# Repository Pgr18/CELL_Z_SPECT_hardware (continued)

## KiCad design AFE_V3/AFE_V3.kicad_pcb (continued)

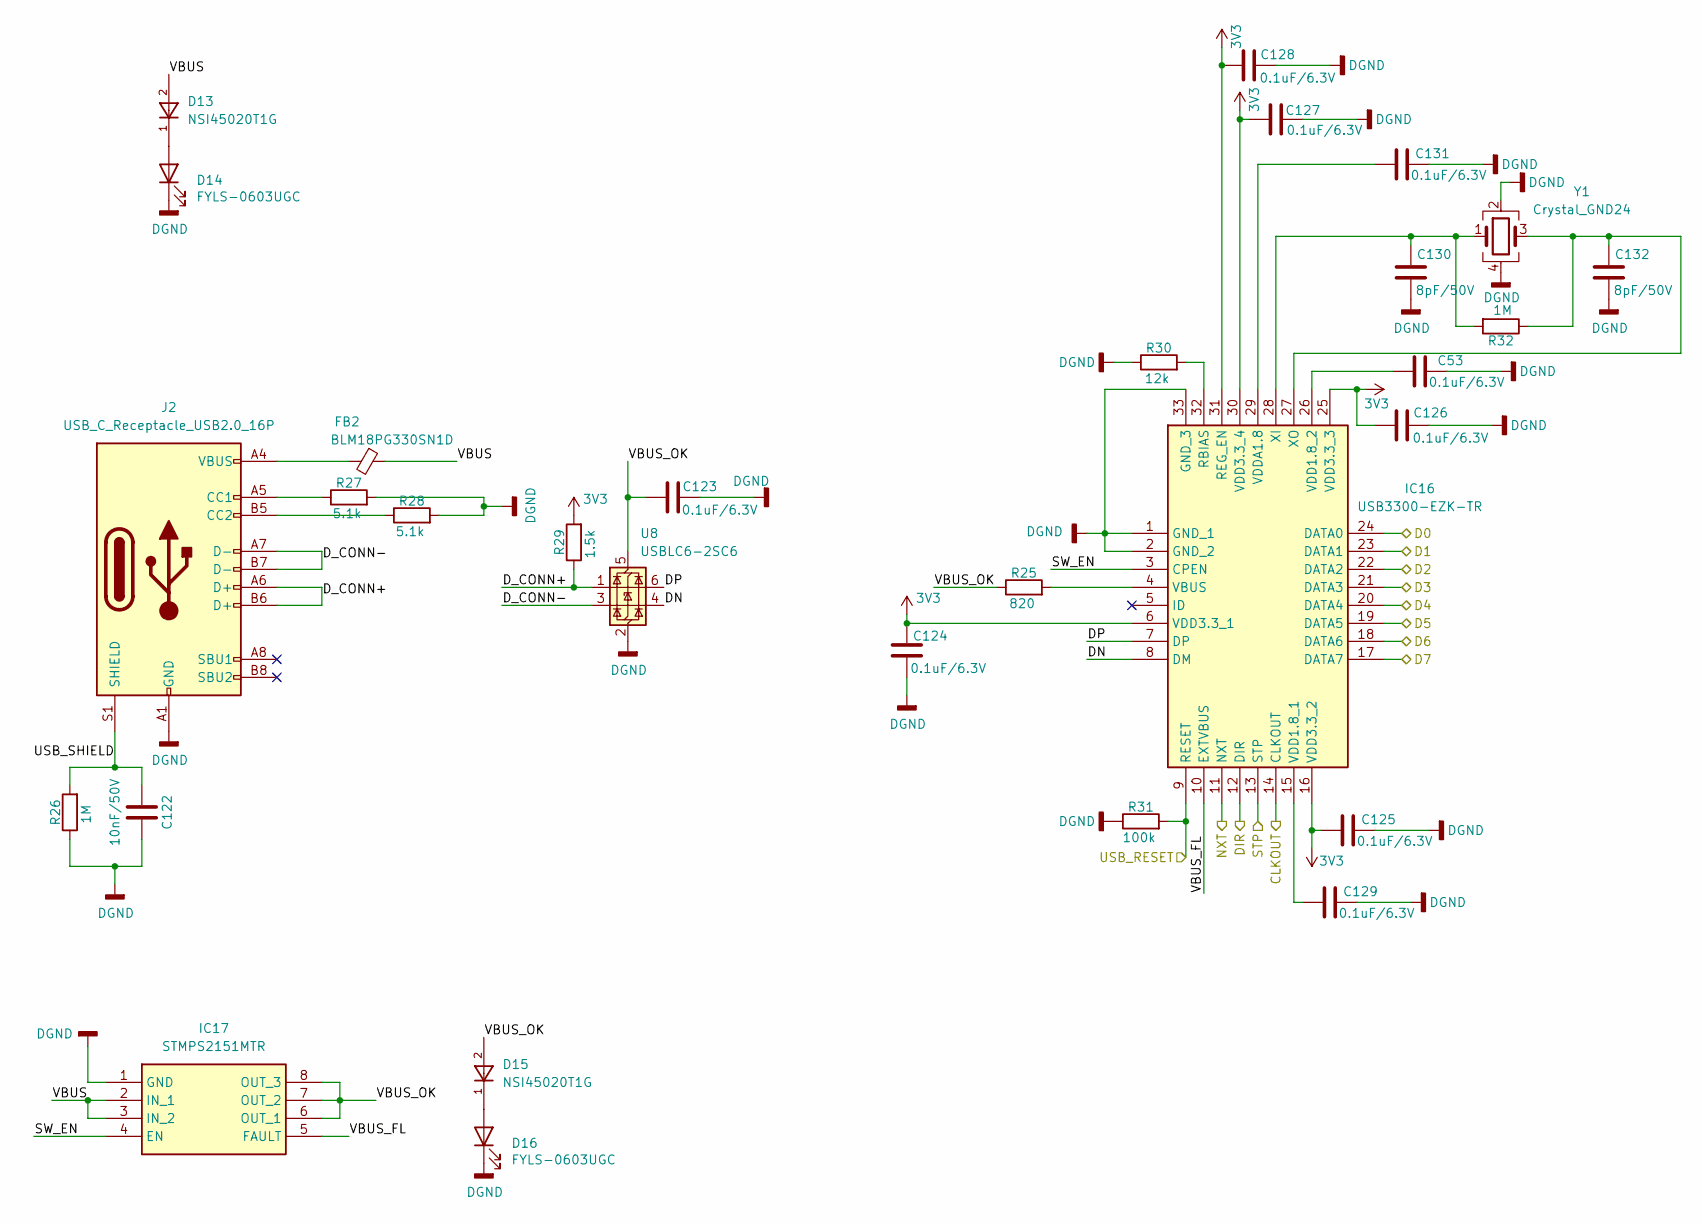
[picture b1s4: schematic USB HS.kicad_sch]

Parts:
C53, C123, C124, C125, C126, C127, C128, C129, C131: 0.1uF/6.3V; C_0603_1608Metric_Pad1.08x0.95mm_HandSolder
C122: 10nF/50V; C_0603_1608Metric_Pad1.08x0.95mm_HandSolder
C130, C132: 8pF/50V; C_0402_1005Metric_Pad0.74x0.62mm_HandSolder
D13, D15: NSI45020T1G; SOD3716X135N; PARTREV 6
D14, D16: FYLS-0603UGC; LED_0603_1608Metric_Pad1.05x0.95mm_HandSolder
FB2: BLM18PG330SN1D; L_0603_1608Metric_Pad1.05x0.95mm_HandSolder
IC16: USB3300-EZK-TR; QFN50P500X500X100-33N-D; Manufacturer_Part_Number USB3300-EZK-TR
IC17: STMPS2151MTR; SOIC127P600X175-8N; Manufacturer_Part_Number STMPS2151MTR; Mouser Part Number 511-STMPS2151MTR
J2: USB_C_Receptacle_USB2.0_16P; USB_C_Receptacle_GCT_USB4110
R25: 820; R_0805_2012Metric_Pad1.20x1.40mm_HandSolder
R26, R32: 1M; R_0805_2012Metric_Pad1.20x1.40mm_HandSolder
R27, R28: 5.1k; R_0603_1608Metric_Pad0.98x0.95mm_HandSolder
R29: 1.5k; R_0603_1608Metric_Pad0.98x0.95mm_HandSolder
R30: 12k; R_0805_2012Metric_Pad1.20x1.40mm_HandSolder
R31: 100k; R_0603_1608Metric
U8: USBLC6-2SC6; SOT-23-6
Y1: Crystal_GND24; Crystal_SMD_SeikoEpson_FA238-4Pin_3.2x2.5mm

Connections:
3V3: C124.1, C125.1, C126.1, C127.1, C128.1, IC16.6 (VDD3.3_1), IC16.16 (VDD3.3_2), IC16.25 (VDD3.3_3), IC16.30 (VDD3.3_4), IC16.31 (REG_EN), R29.2; also elsewhere on the board
/ULPI_CK: IC16.14 (CLKOUT); also elsewhere on the board
/ULPI_D0: IC16.24 (DATA0); also elsewhere on the board
/ULPI_D1: IC16.23 (DATA1); also elsewhere on the board
/ULPI_D2: IC16.22 (DATA2); also elsewhere on the board
/ULPI_D3: IC16.21 (DATA3); also elsewhere on the board
/ULPI_D4: IC16.20 (DATA4); also elsewhere on the board
/ULPI_D5: IC16.19 (DATA5); also elsewhere on the board
/ULPI_D6: IC16.18 (DATA6); also elsewhere on the board
/ULPI_D7: IC16.17 (DATA7); also elsewhere on the board
/ULPI_DIR: IC16.12 (DIR); also elsewhere on the board
/ULPI_NXT: IC16.11 (NXT); also elsewhere on the board
/ULPI_STP: IC16.13 (STP); also elsewhere on the board
/USB HS/DN: IC16.8 (DM), U8.4 (I/O2)
/USB HS/DP: IC16.7 (DP), U8.6 (I/O1)
/USB HS/D_CONN+: J2.A6 (D+), J2.B6 (D+), R29.1, U8.1 (I/O1)
/USB HS/D_CONN-: J2.A7 (D-), J2.B7 (D-), U8.3 (I/O2)
/USB HS/SW_EN: IC16.3 (CPEN), IC17.4 (EN)
/USB HS/USB_SHIELD: C122.1, J2.S1 (SHIELD), R26.2
/USB HS/VBUS: D13.2, FB2.1, IC17.2 (IN_1), IC17.3 (IN_2)
/USB HS/VBUS_FL: IC16.10 (EXTVBUS), IC17.5 (FAULT)
/USB HS/VBUS_OK: C123.2, D15.2, IC17.6 (OUT_1), IC17.7 (OUT_2), IC17.8 (OUT_3), R25.1, U8.5 (VBUS)
/USB_RESET: IC16.9 (RESET), R31.2; also elsewhere on the board
DGND: C53.2, C122.2, C123.1, C124.2, C125.2, C126.2, C127.2, C128.2, C129.2, C130.1, C131.2, C132.1, D14.1 (K), D16.1 (K), IC16.1 (GND_1), IC16.2 (GND_2), IC16.33 (GND_3), IC17.1 (GND), J2.A1 (GND), J2.A12 (GND), J2.B1 (GND), J2.B12 (GND), R26.1, R27.2, R28.2, R30.1, R31.1, U8.2 (GND), Y1.2, Y1.4; also elsewhere on the board
unnamed: D13.1, D14.2 (A)
unnamed: D15.1, D16.2 (A)
unnamed: FB2.2, J2.A4 (VBUS), J2.A9 (VBUS), J2.B4 (VBUS), J2.B9 (VBUS)
unnamed: IC16.32 (RBIAS), R30.2
unnamed: IC16.4 (VBUS), R25.2
unnamed: C129.1, IC16.15 (VDD1.8_1)
unnamed: C53.1, IC16.26 (VDD1.8_2)
unnamed: C131.1, IC16.29 (VDDA1.8)
unnamed: C130.2, IC16.28 (XI), R32.2, Y1.1
unnamed: C132.2, IC16.27 (XO), R32.1, Y1.3
unnamed: J2.A5 (CC1), R27.1
unnamed: J2.B5 (CC2), R28.1

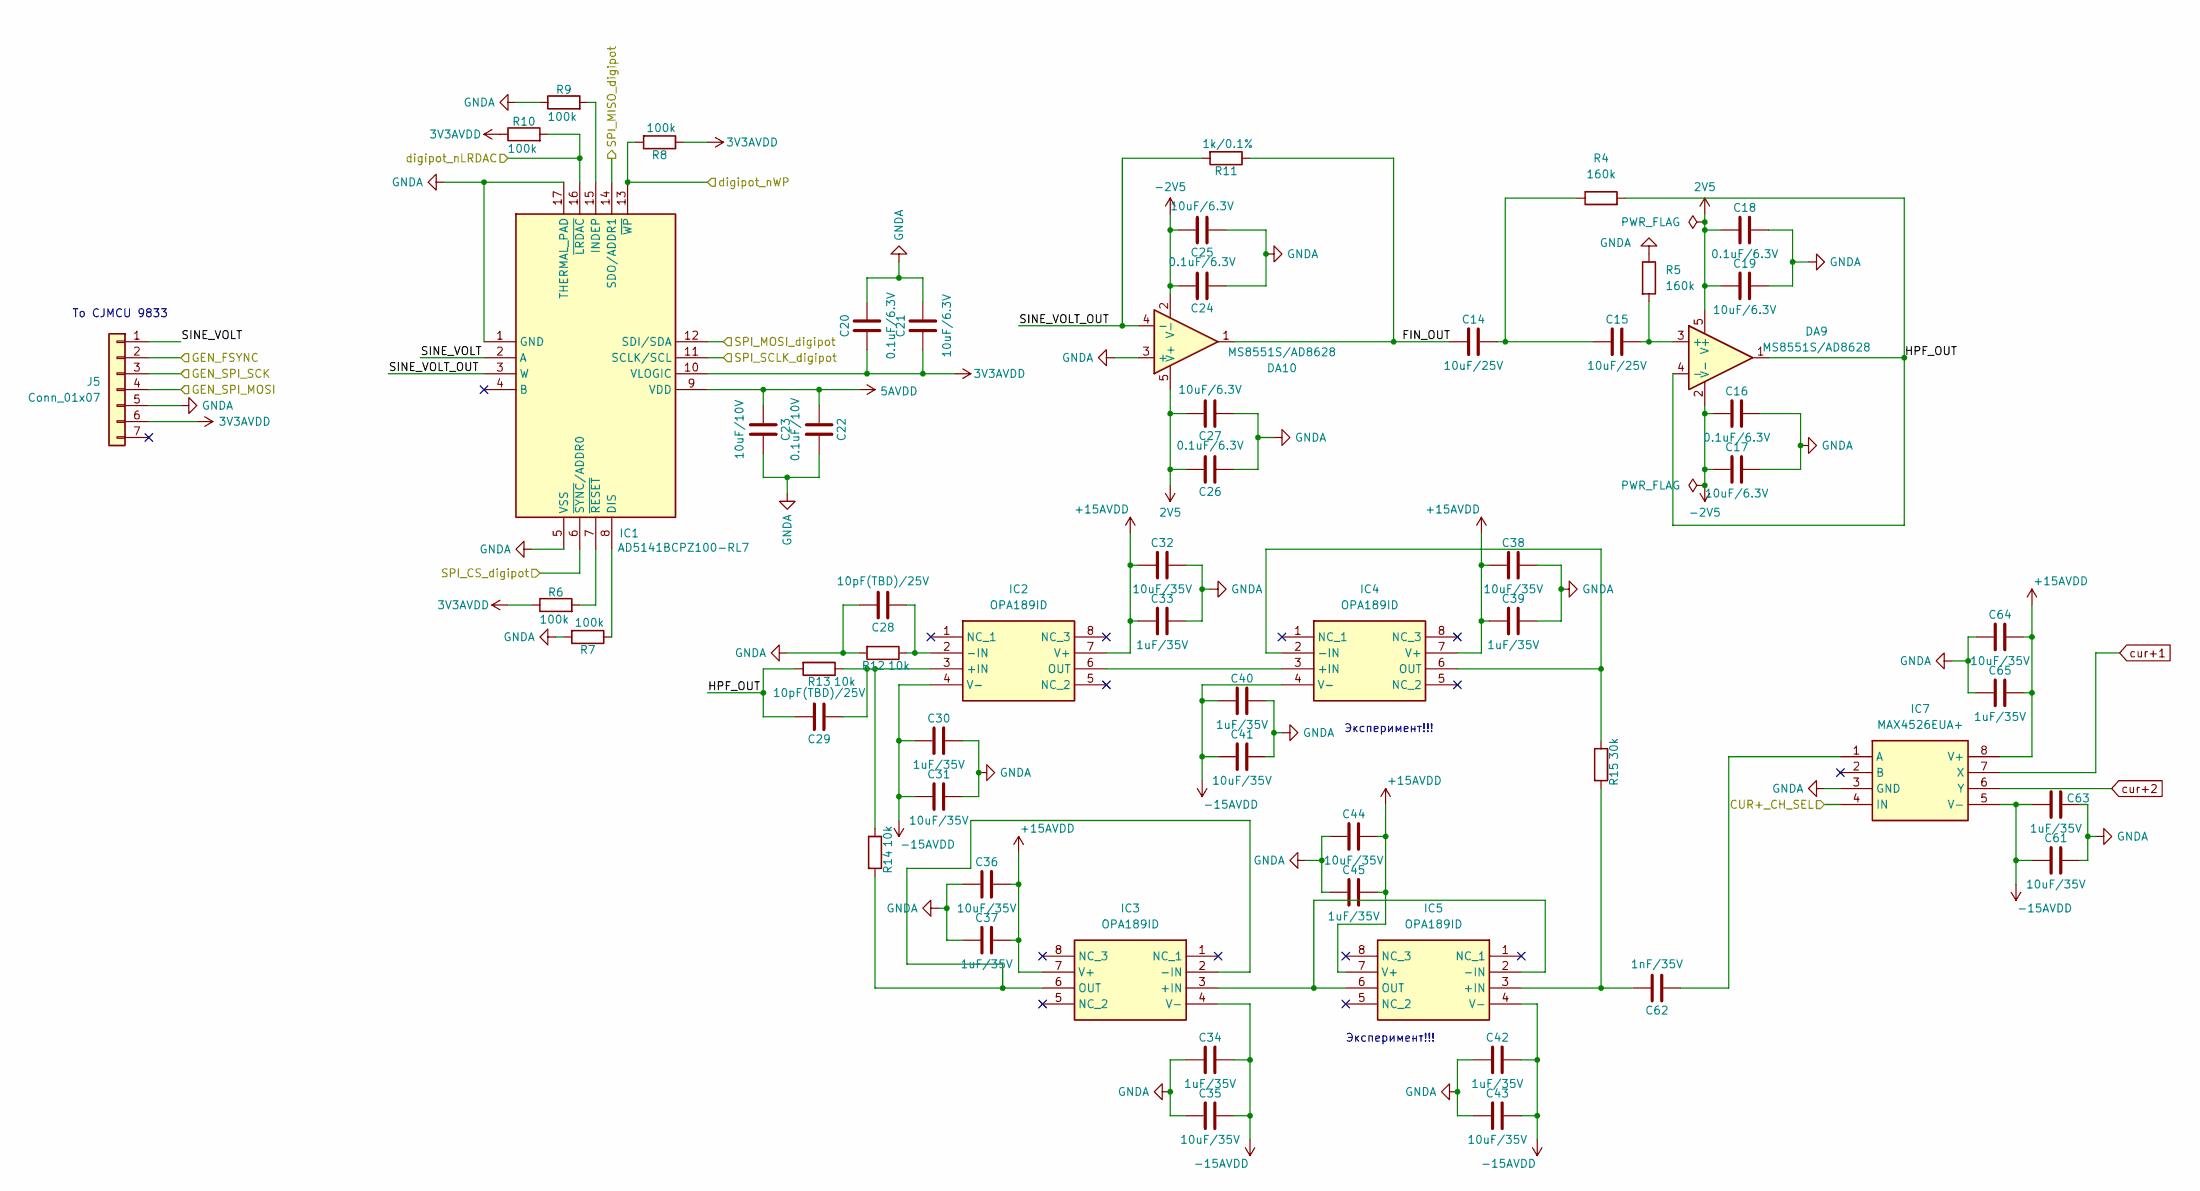
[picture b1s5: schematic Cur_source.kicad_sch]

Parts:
C14, C15: 10uF/25V; C_0805_2012Metric_Pad1.18x1.45mm_HandSolder
C16, C18, C20, C24, C26: 0.1uF/6.3V; C_0603_1608Metric_Pad1.08x0.95mm_HandSolder
C17, C19, C21, C25, C27: 10uF/6.3V; C_0805_2012Metric_Pad1.18x1.45mm_HandSolder
C22: 0.1uF/10V; C_0603_1608Metric_Pad1.08x0.95mm_HandSolder
C23: 10uF/10V; C_0805_2012Metric_Pad1.18x1.45mm_HandSolder
C28, C29: 10pF(TBD)/25V; C_0805_2012Metric_Pad1.18x1.45mm_HandSolder
C30, C33, C34, C37, C39, C40, C42, C45, C63, C65: 1uF/35V; C_0603_1608Metric_Pad1.08x0.95mm_HandSolder
C31, C32, C35, C36, C38, C41, C43, C44, C61, C64: 10uF/35V; C_0805_2012Metric_Pad1.18x1.45mm_HandSolder
C62: 1nF/35V; C_0603_1608Metric_Pad1.08x0.95mm_HandSolder
DA9, DA10: MS8551S/AD8628; SOT-23-5
IC1: AD5141BCPZ100-RL7; QFN50P300X300X80-17N-D; Manufacturer_Part_Number AD5141BCPZ100-RL7; Mouser Part Number 584-AD5141BCPZ100-R7
IC2, IC3, IC4, IC5: OPA189ID; SOIC127P600X175-8N; Manufacturer_Part_Number OPA189ID; Mouser Part Number 595-OPA189ID
IC7: MAX4526EUA+; SOIC127P600X175-8N; Manufacturer_Part_Number MAX4526CSA+; Mouser Part Number 700-MAX4526CSA
J5: Conn_01x07; PinHeader_1x07_P2.54mm_Vertical
R4, R5: 160k; R_0603_1608Metric_Pad0.98x0.95mm_HandSolder
R6, R7, R8, R9, R10: 100k; R_0603_1608Metric_Pad0.98x0.95mm_HandSolder
R11: 1k/0.1%; R_0603_1608Metric_Pad0.98x0.95mm_HandSolder
R12, R13, R14: 10k; R_0603_1608Metric_Pad0.98x0.95mm_HandSolder
R15: 30k; R_0603_1608Metric_Pad0.98x0.95mm_HandSolder

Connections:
2V5: C18.2, C19.2, C26.2, C27.2, DA9.5 (V+), DA10.5 (V+); also elsewhere on the board
3V3AVDD: C20.2, C21.2, IC1.10 (VLOGIC), J5.6, R6.1, R8.1, R10.1; also elsewhere on the board
5AVDD: C22.2, C23.2, IC1.9 (VDD); also elsewhere on the board
+15AVDD: C32.2, C33.2, C36.2, C37.2, C38.2, C39.2, C44.2, C45.2, C64.2, C65.2, IC2.7 (V+), IC3.7 (V+), IC4.7 (V+), IC5.7 (V+), IC7.8 (V+); also elsewhere on the board
-2V5: C16.2, C17.2, C24.2, C25.2, DA9.2 (V-), DA10.2 (V-); also elsewhere on the board
-15AVDD: C30.2, C31.2, C34.2, C35.2, C40.2, C41.2, C42.2, C43.2, C61.2, C63.2, IC2.4 (V-), IC3.4 (V-), IC4.4 (V-), IC5.4 (V-), IC7.5 (V-); also elsewhere on the board
/CUR+_CH_SEL: IC7.4 (IN); also elsewhere on the board
/Current_source/FIN_OUT: C14.2, DA10.1, R11.1
/Current_source/GEN_FSYNC: J5.2; also elsewhere on the board
/Current_source/GEN_SPI_MOSI: J5.4; also elsewhere on the board
/Current_source/GEN_SPI_SCK: J5.3; also elsewhere on the board
/Current_source/HPF_OUT: C29.2, DA9.1, DA9.4 (-), R4.2, R13.2
/Current_source/SINE_VOLT: IC1.2 (A), J5.1
/Current_source/SINE_VOLT_OUT: DA10.4 (-), IC1.3 (W), R11.2
/Current_source/SPI_CS_digipot: IC1.6 (~SYNC/ADDR0); also elsewhere on the board
/Current_source/SPI_MISO_digipot: IC1.14 (SDO/ADDR1); also elsewhere on the board
/Current_source/SPI_MOSI_digipot: IC1.12 (SDI/SDA); also elsewhere on the board
/Current_source/SPI_SCLK_digipot: IC1.11 (SCLK/SCL); also elsewhere on the board
/Current_source/digipot_nLRDAC: IC1.16 (~LRDAC), R10.2; also elsewhere on the board
/Current_source/digipot_nWP: IC1.13 (~WP), R8.2; also elsewhere on the board
GNDA: C16.1, C17.1, C18.1, C19.1, C20.1, C21.1, C22.1, C23.1, C24.1, C25.1, C26.1, C27.1, C28.2, C30.1, C31.1, C32.1, C33.1, C34.1, C35.1, C36.1, C37.1, C38.1, C39.1, C40.1, C41.1, C42.1, C43.1, C44.1, C45.1, C61.1, C63.1, C64.1, C65.1, DA10.3 (+), IC1.1 (GND), IC1.5 (VSS), IC1.17 (THERMAL_PAD), IC7.3 (GND), J5.5, R5.1, R7.2, R9.1, R12.2; also elsewhere on the board
unnamed: C14.1, C15.2, R4.1
unnamed: C15.1, DA9.3 (+), R5.2
unnamed: IC1.8 (DIS), R7.1
unnamed: IC1.15 (INDEP), R9.2
unnamed: IC1.7 (~RESET), R6.2
unnamed: C29.1, IC2.3 (+IN), R13.1, R14.1
unnamed: C28.1, IC2.2 (-IN), R12.1
unnamed: IC2.6 (OUT), IC4.3 (+IN)
unnamed: IC3.3 (+IN), IC5.2 (-IN), IC5.6 (OUT)
unnamed: IC3.2 (-IN), IC3.6 (OUT), R14.2
unnamed: IC4.2 (-IN), IC4.6 (OUT), R15.1
unnamed: C62.2, IC5.3 (+IN), R15.2
unnamed: C62.1, IC7.1 (A)
cur+1: IC7.7 (X); also elsewhere on the board
cur+2: IC7.6 (Y); also elsewhere on the board

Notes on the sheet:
Эксперимент!!!
To CJMCU 9833

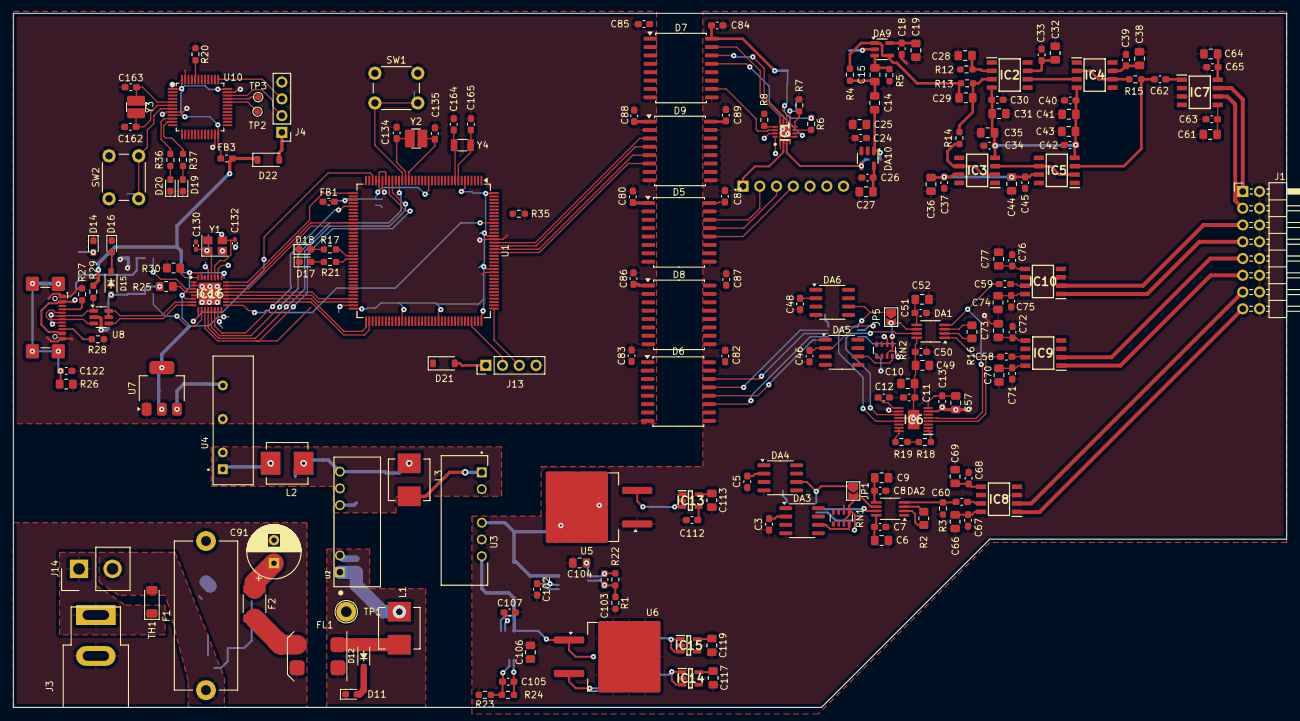
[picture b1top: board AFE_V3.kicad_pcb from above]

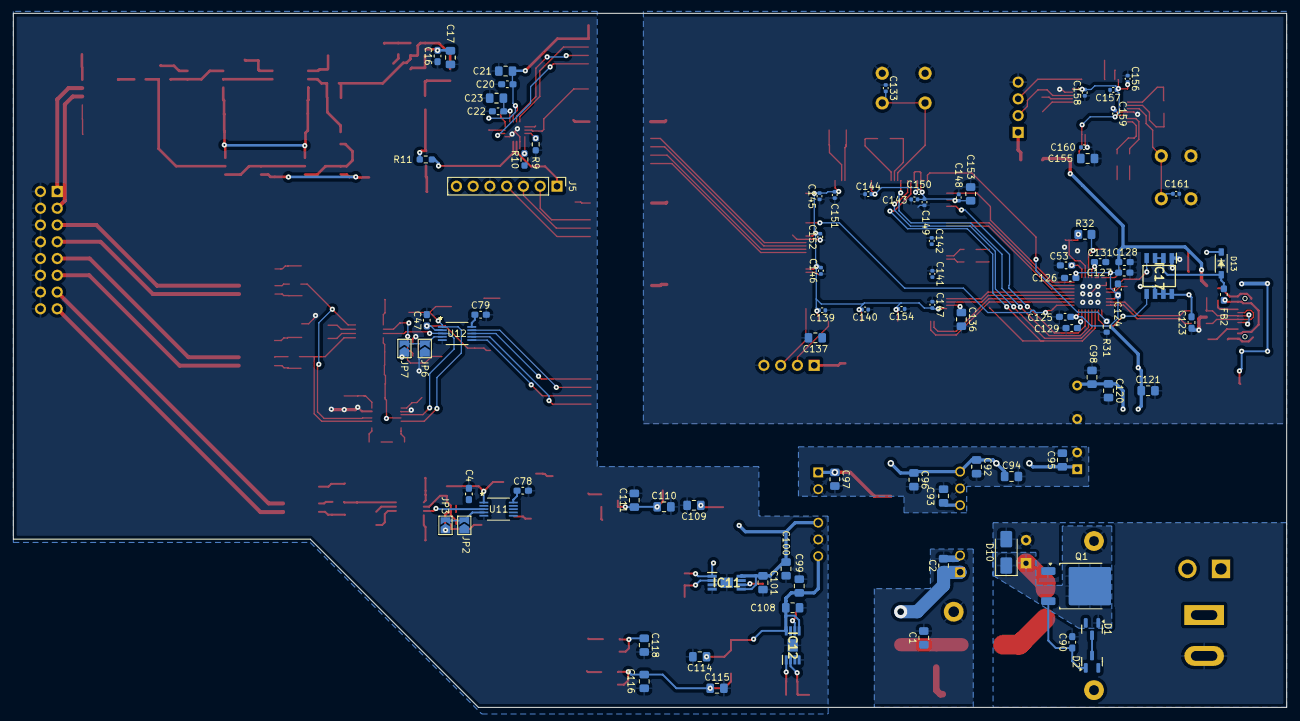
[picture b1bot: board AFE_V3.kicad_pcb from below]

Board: 2 copper layers, 193.0 x 105.2 mm, 287 parts (89 on the bottom side), 184 nets.

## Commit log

2024-05-27 Added AFE_V3_project
2024-08-03 Added new files:lib and pcb
2024-08-03 Started pcb placing
2024-08-04 PCB tracing in progress. Added some 3d models
2024-08-09 PCB tracing in progress
2024-08-11 PCB Tracing done. Added CI files
2024-08-11 Final done
2024-08-11 smth not important
2024-08-11 Added logo
2024-08-11 nothing important
2024-09-12 Corrected schematic
2024-09-12 smth
2024-09-21 Fresh version
2024-11-19 Перед передачей
